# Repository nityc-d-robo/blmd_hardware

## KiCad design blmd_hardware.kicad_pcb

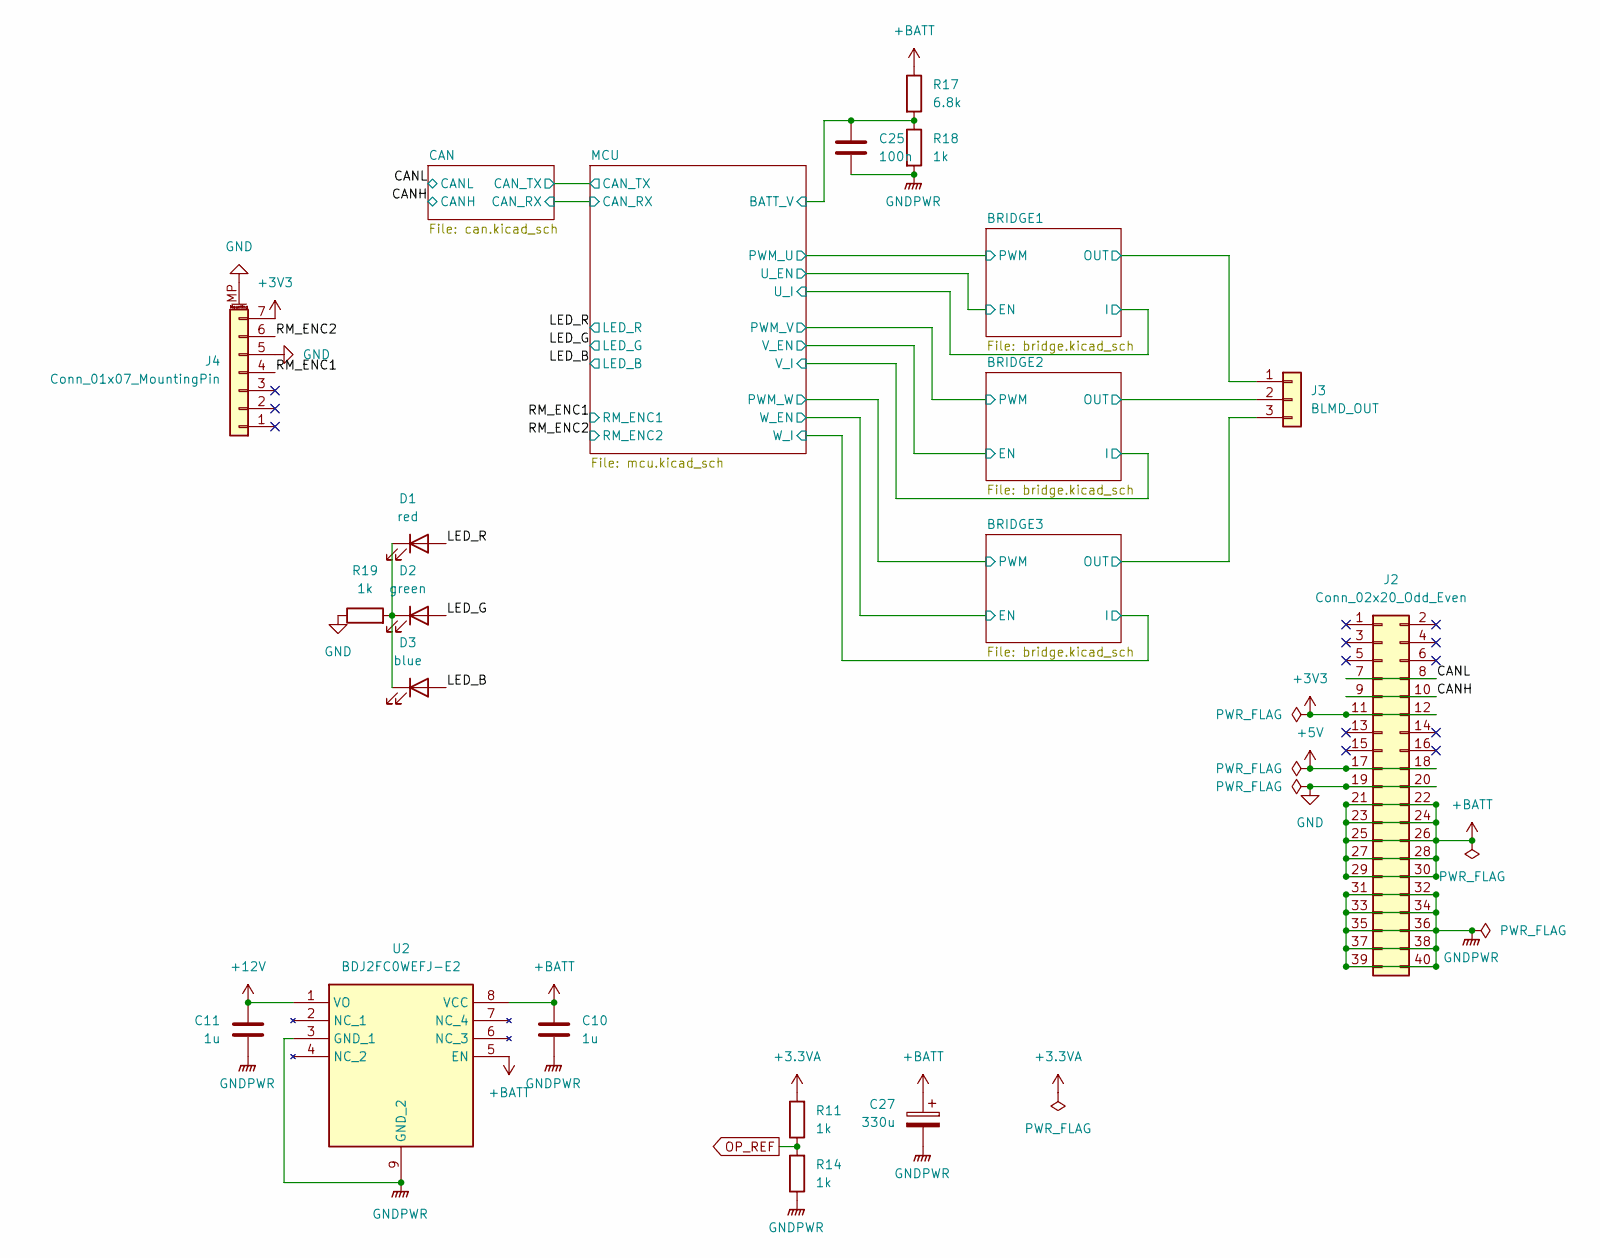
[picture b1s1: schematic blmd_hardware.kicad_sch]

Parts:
C10, C11: 1u; C_0603_1608Metric_Pad1.08x0.95mm_HandSolder
C25: 100n; C_0603_1608Metric_Pad1.08x0.95mm_HandSolder
C27: 330u; CP_Elec_10x12.6
D1: red; LED_0603_1608Metric_Pad1.05x0.95mm_HandSolder
D2: green; LED_0603_1608Metric_Pad1.05x0.95mm_HandSolder
D3: blue; LED_0603_1608Metric_Pad1.05x0.95mm_HandSolder
J2: Conn_02x20_Odd_Even; PinHeader_2x20_P2.54mm_Horizontal
J3: BLMD_OUT; AMASS_MR30PW-FB_1x03_P3.50mm_Horizontal
J4: Conn_01x07_MountingPin; JST_GH_SM07B-GHS-TB_1x07-1MP_P1.25mm_Horizontal
R11, R14, R18, R19: 1k; R_0603_1608Metric_Pad0.98x0.95mm_HandSolder
R17: 6.8k; R_0603_1608Metric_Pad0.98x0.95mm_HandSolder
U2: BDJ2FC0WEFJ-E2; SOIC127P600X100-9N; Manufacturer_Part_Number BDJ2FC0WEFJ-E2

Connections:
+3.3VA: R11.2; also elsewhere on the board
+5V: J2.17, J2.18
+12V: C11.2, U2.1 (VO); also elsewhere on the board
+BATT: C10.2, C27.1, J2.21, J2.22, J2.23, J2.24, J2.25, J2.26, J2.27, J2.28, J2.29, J2.30, R17.1, U2.5 (EN), U2.8 (VCC); also elsewhere on the board
/BRIDGE1/OUT: J3.1; also elsewhere on the board
/BRIDGE2/OUT: J3.2; also elsewhere on the board
/BRIDGE3/OUT: J3.3; also elsewhere on the board
/CANH: J2.9, J2.10; also elsewhere on the board
/CANL: J2.7, J2.8; also elsewhere on the board
/LED_B: D3.2 (A); also elsewhere on the board
/LED_G: D2.2 (A); also elsewhere on the board
/LED_R: D1.2 (A); also elsewhere on the board
/MCU/BATT_V: C25.1, R17.2, R18.1; also elsewhere on the board
/RM_ENC1: J4.4; also elsewhere on the board
/RM_ENC2: J4.6; also elsewhere on the board
GND: J2.19, J2.20, J4.5, J4.MP (MountPin), R19.1; also elsewhere on the board
unnamed: D1.1 (K), D2.1 (K), D3.1 (K), R19.2

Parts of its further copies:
R12: 1k; R_0603_1608Metric_Pad0.98x0.95mm_HandSolder

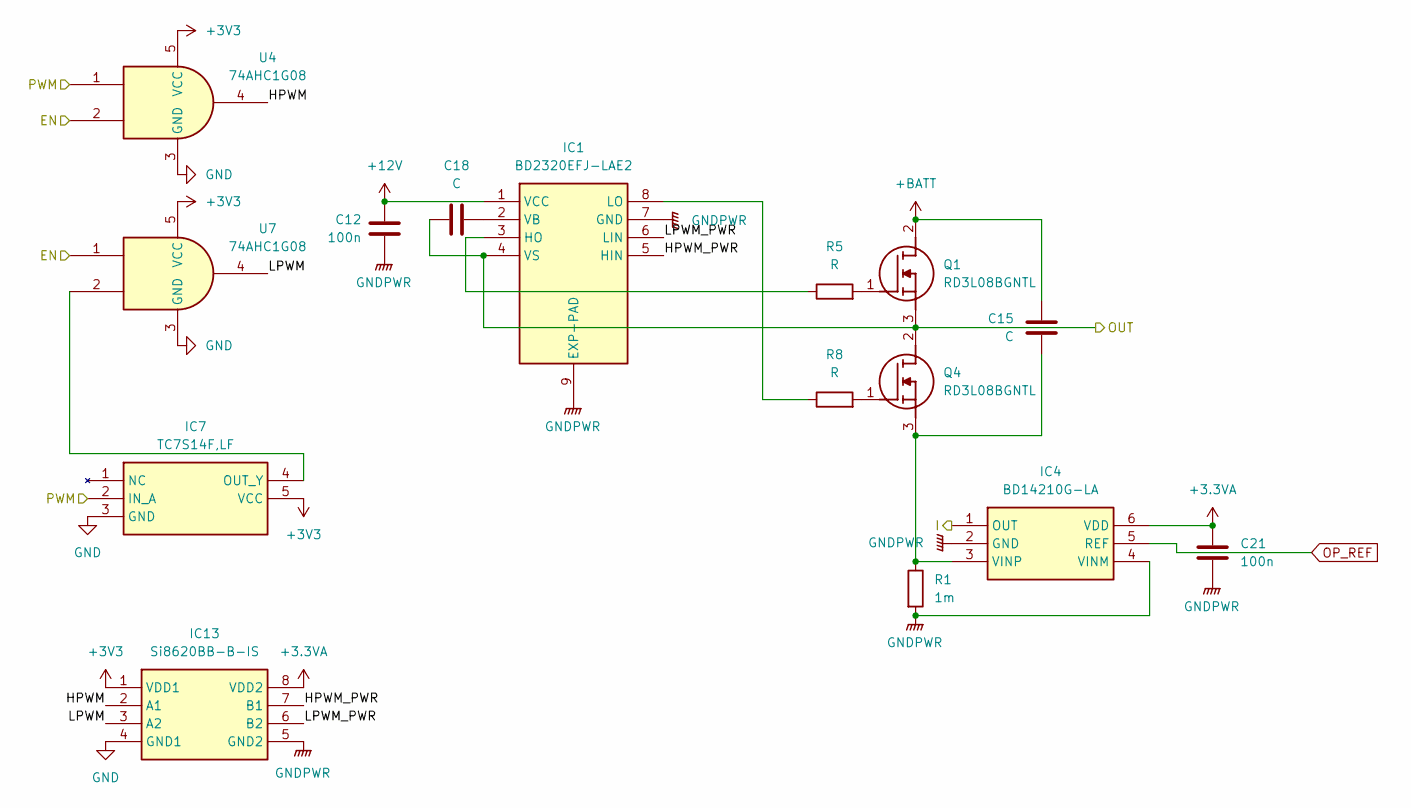
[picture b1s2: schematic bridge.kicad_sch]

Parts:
C12, C21: 100n; C_0603_1608Metric_Pad1.08x0.95mm_HandSolder
C15, C18: C; C_0603_1608Metric_Pad1.08x0.95mm_HandSolder
IC1: BD2320EFJ-LAE2; SOIC127P600X100-9N; Manufacturer_Part_Number BD2320EFJ-LAE2
IC4: BD14210G-LA; SOP95P280X125-6N; Manufacturer_Part_Number BD14210G-LA
IC7: TC7S14F,LF; SOT95P275X140-5N; Manufacturer_Part_Number TC7S14F,LF
IC13: Si8620BB-B-IS; SOIC127P600X175-8N; Manufacturer_Part_Number Si8620BB-B-IS
Q1, Q4: RD3L08BGNTL; RD3P175SNFRATL; Manufacturer_Part_Number RD3L08BGNTL; Mouser Part Number 755-RD3L08BGNTL
R1: 1m; R_0603_1608Metric_Pad0.98x0.95mm_HandSolder
R5, R8: R; R_0603_1608Metric_Pad0.98x0.95mm_HandSolder
U4, U7: 74AHC1G08; SOT95P275X140-5N

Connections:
+3.3VA: C21.1, IC4.6 (VDD), IC13.8 (VDD2); also elsewhere on the board
+12V: C12.2, IC1.1 (VCC); also elsewhere on the board
+BATT: C15.1, Q1.2 (D); also elsewhere on the board
/BRIDGE1/EN: U4.2, U7.1; also elsewhere on the board
/BRIDGE1/HPWM: IC13.2 (A1), U4.4
/BRIDGE1/HPWM_PWR: IC1.5 (HIN), IC13.7 (B1)
/BRIDGE1/I: IC4.1 (OUT); also elsewhere on the board
/BRIDGE1/LPWM: IC13.3 (A2), U7.4
/BRIDGE1/LPWM_PWR: IC1.6 (LIN), IC13.6 (B2)
/BRIDGE1/OUT: C18.1, IC1.4 (VS), Q1.3 (S), Q4.2 (D); also elsewhere on the board
/BRIDGE1/PWM: IC7.2 (IN_A), U4.1; also elsewhere on the board
GND: IC7.3 (GND), IC13.4 (GND1), U4.3 (GND), U7.3 (GND); also elsewhere on the board
unnamed: IC1.3 (HO), R5.1
unnamed: IC1.8 (LO), R8.1
unnamed: C18.2, IC1.2 (VB)
unnamed: C15.2, IC4.3 (VINP), Q4.3 (S), R1.1
unnamed: IC7.4 (OUT_Y), U7.2
unnamed: Q1.1 (G), R5.2
unnamed: Q4.1 (G), R8.2

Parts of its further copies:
C13, C14, C22, C23: 100n; C_0603_1608Metric_Pad1.08x0.95mm_HandSolder
C16, C17, C19, C20: C; C_0603_1608Metric_Pad1.08x0.95mm_HandSolder
IC2, IC3: BD2320EFJ-LAE2; SOIC127P600X100-9N; Manufacturer_Part_Number BD2320EFJ-LAE2
IC5, IC6: BD14210G-LA; SOP95P280X125-6N; Manufacturer_Part_Number BD14210G-LA
IC8, IC9: TC7S14F,LF; SOT95P275X140-5N; Manufacturer_Part_Number TC7S14F,LF
IC14, IC15: Si8620BB-B-IS; SOIC127P600X175-8N; Manufacturer_Part_Number Si8620BB-B-IS
Q2, Q3, Q5, Q6: RD3L08BGNTL; RD3P175SNFRATL; Manufacturer_Part_Number RD3L08BGNTL; Mouser Part Number 755-RD3L08BGNTL
R2, R3: 1m; R_0603_1608Metric_Pad0.98x0.95mm_HandSolder
R6, R7, R9, R10: R; R_0603_1608Metric_Pad0.98x0.95mm_HandSolder
U5, U6, U8, U9: 74AHC1G08; SOT95P275X140-5N

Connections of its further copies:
+3.3VA: C22.1, C23.1, IC5.6 (VDD), IC6.6 (VDD), IC14.8 (VDD2), IC15.8 (VDD2); also elsewhere on the board
+12V: C13.2, C14.2, IC2.1 (VCC), IC3.1 (VCC); also elsewhere on the board
+BATT: C16.1, C17.1, Q2.2 (D), Q3.2 (D); also elsewhere on the board
/BRIDGE2/EN: U5.2, U8.1; also elsewhere on the board
/BRIDGE2/HPWM: IC14.2 (A1), U5.4
/BRIDGE2/HPWM_PWR: IC2.5 (HIN), IC14.7 (B1)
/BRIDGE2/I: IC5.1 (OUT); also elsewhere on the board
/BRIDGE2/LPWM: IC14.3 (A2), U8.4
/BRIDGE2/LPWM_PWR: IC2.6 (LIN), IC14.6 (B2)
/BRIDGE2/OUT: C19.1, IC2.4 (VS), Q2.3 (S), Q5.2 (D); also elsewhere on the board
/BRIDGE2/PWM: IC8.2 (IN_A), U5.1; also elsewhere on the board
/BRIDGE3/EN: U6.2, U9.1; also elsewhere on the board
/BRIDGE3/HPWM: IC15.2 (A1), U6.4
/BRIDGE3/HPWM_PWR: IC3.5 (HIN), IC15.7 (B1)
/BRIDGE3/I: IC6.1 (OUT); also elsewhere on the board
/BRIDGE3/LPWM: IC15.3 (A2), U9.4
/BRIDGE3/LPWM_PWR: IC3.6 (LIN), IC15.6 (B2)
/BRIDGE3/OUT: C20.1, IC3.4 (VS), Q3.3 (S), Q6.2 (D); also elsewhere on the board
/BRIDGE3/PWM: IC9.2 (IN_A), U6.1; also elsewhere on the board
GND: IC8.3 (GND), IC9.3 (GND), IC14.4 (GND1), IC15.4 (GND1), U5.3 (GND), U6.3 (GND), U8.3 (GND), U9.3 (GND); also elsewhere on the board
unnamed: IC2.3 (HO), R6.1
unnamed: IC2.8 (LO), R9.1
unnamed: C19.2, IC2.2 (VB)
unnamed: IC3.3 (HO), R7.1
unnamed: IC3.8 (LO), R10.1
unnamed: C20.2, IC3.2 (VB)
unnamed: C16.2, IC5.3 (VINP), Q5.3 (S), R2.1
unnamed: C17.2, IC6.3 (VINP), Q6.3 (S), R3.1
unnamed: IC8.4 (OUT_Y), U8.2
unnamed: IC9.4 (OUT_Y), U9.2
unnamed: Q2.1 (G), R6.2
unnamed: Q3.1 (G), R7.2
unnamed: Q5.1 (G), R9.2
unnamed: Q6.1 (G), R10.2

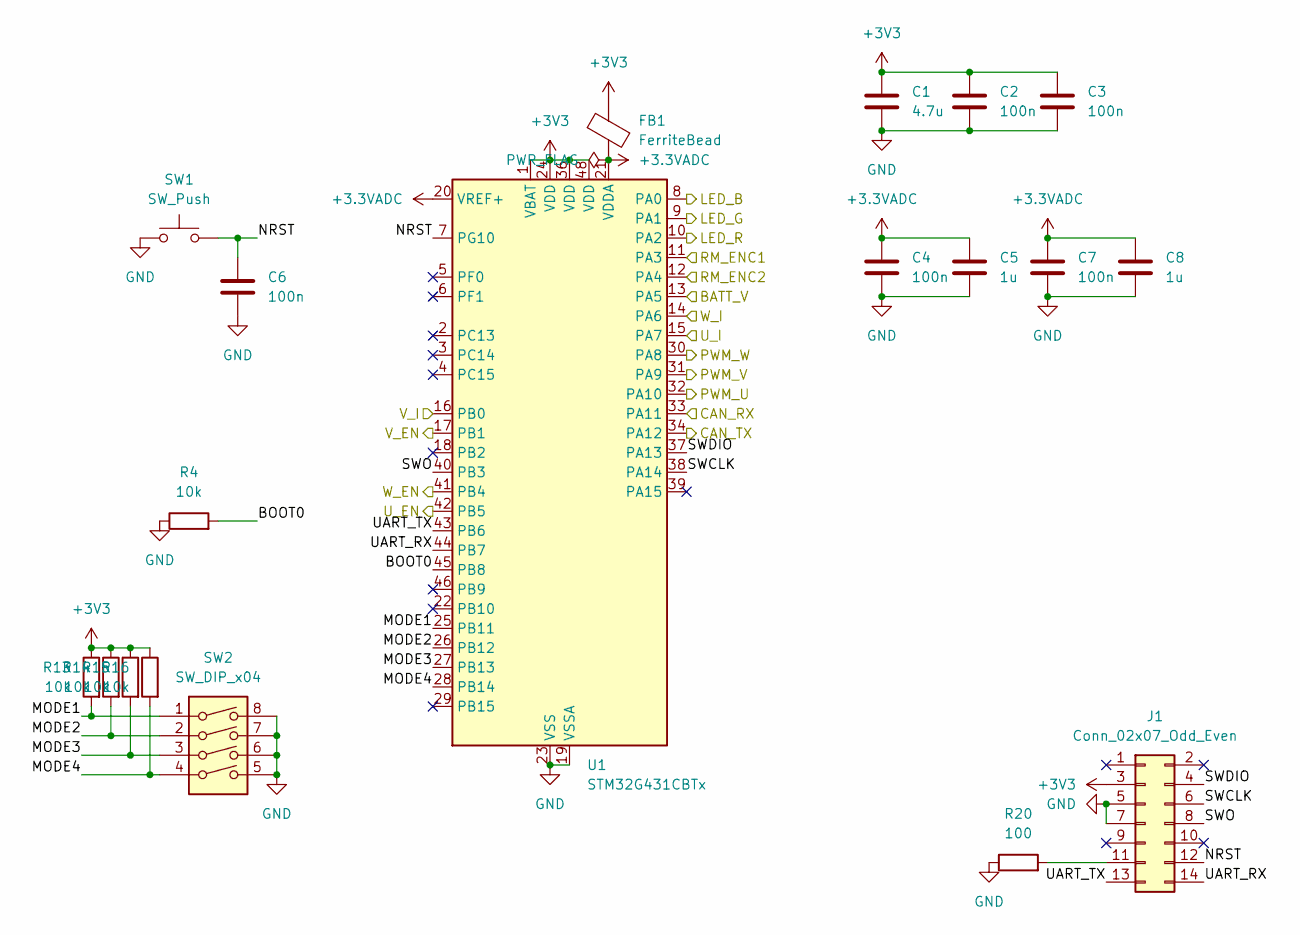
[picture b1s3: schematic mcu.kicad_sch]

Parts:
C1: 4.7u; C_0603_1608Metric_Pad1.08x0.95mm_HandSolder
C2, C3, C4, C6, C7: 100n; C_0603_1608Metric_Pad1.08x0.95mm_HandSolder
C5, C8: 1u; C_0603_1608Metric_Pad1.08x0.95mm_HandSolder
FB1: FerriteBead; C_0603_1608Metric_Pad1.08x0.95mm_HandSolder
J1: Conn_02x07_Odd_Even; PinHeader_2x07_P1.27mm_Vertical
R4, R13, R14, R15, R16: 10k; R_0603_1608Metric_Pad0.98x0.95mm_HandSolder
R20: 100; R_0603_1608Metric_Pad0.98x0.95mm_HandSolder
SW1: SW_Push; TVAF06-A020B-R
SW2: SW_DIP_x04; SW_DIP_SPSTx04_Slide_Copal_CHS-04B_W7.62mm_P1.27mm
U1: STM32G431CBTx; LQFP-48_7x7mm_P0.5mm

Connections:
+3.3VADC: C4.1, C5.1, C7.1, C8.1, FB1.2, U1.20 (VREF+), U1.21 (VDDA)
/BRIDGE1/EN: U1.42 (PB5); also elsewhere on the board
/BRIDGE1/I: U1.15 (PA7); also elsewhere on the board
/BRIDGE1/PWM: U1.32 (PA10); also elsewhere on the board
/BRIDGE2/EN: U1.17 (PB1); also elsewhere on the board
/BRIDGE2/I: U1.16 (PB0); also elsewhere on the board
/BRIDGE2/PWM: U1.31 (PA9); also elsewhere on the board
/BRIDGE3/EN: U1.41 (PB4); also elsewhere on the board
/BRIDGE3/I: U1.14 (PA6); also elsewhere on the board
/BRIDGE3/PWM: U1.30 (PA8); also elsewhere on the board
/CAN/CAN_RX: U1.33 (PA11); also elsewhere on the board
/CAN/CAN_TX: U1.34 (PA12); also elsewhere on the board
/LED_B: U1.8 (PA0); also elsewhere on the board
/LED_G: U1.9 (PA1); also elsewhere on the board
/LED_R: U1.10 (PA2); also elsewhere on the board
/MCU/BATT_V: U1.13 (PA5); also elsewhere on the board
/MCU/BOOT0: R4.2, U1.45 (PB8)
/MCU/MODE1: R13.2, SW2.1, U1.25 (PB11)
/MCU/MODE3: R15.2, SW2.3, U1.27 (PB13)
/MCU/MODE4: R16.2, SW2.4, U1.28 (PB14)
/MCU/NRST: C6.1, J1.12, SW1.2, U1.7 (PG10)
/MCU/SWCLK: J1.6, U1.38 (PA14)
/MCU/SWDIO: J1.4, U1.37 (PA13)
/MCU/SWO: J1.8, U1.40 (PB3)
/MCU/UART_RX: J1.14, U1.44 (PB7)
/MCU/UART_TX: J1.13, U1.43 (PB6)
/RM_ENC1: U1.11 (PA3); also elsewhere on the board
/RM_ENC2: U1.12 (PA4); also elsewhere on the board
GND: C1.2, C2.2, C3.2, C4.2, C5.2, C6.2, C7.2, C8.2, J1.5, J1.7, R4.1, R20.1, SW1.1, SW2.5, SW2.6, SW2.7, SW2.8, U1.19 (VSSA), U1.23 (VSS), U1.35 (VSS), U1.47 (VSS); also elsewhere on the board
unnamed: J1.11, R20.2

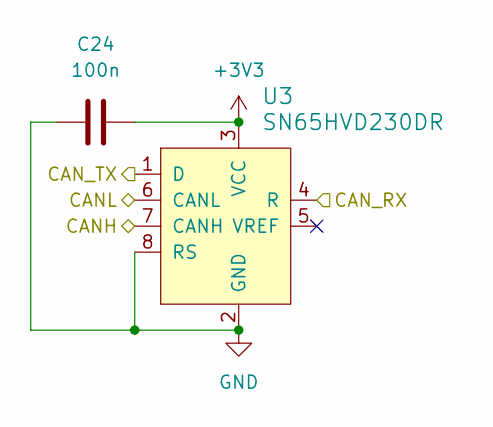
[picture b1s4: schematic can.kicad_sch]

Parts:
C24: 100n; C_0603_1608Metric_Pad1.08x0.95mm_HandSolder
U3: SN65HVD230DR; SOIC-8_3.9x4.9mm_P1.27mm; MPN SN65HVD230DR; Digi-Key_PN 296-11654-1-ND

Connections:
/CAN/CAN_RX: U3.4 (R); also elsewhere on the board
/CAN/CAN_TX: U3.1 (D); also elsewhere on the board
/CANH: U3.7 (CANH); also elsewhere on the board
/CANL: U3.6 (CANL); also elsewhere on the board
GND: C24.1, U3.2 (GND), U3.8 (RS); also elsewhere on the board

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
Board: 2 copper layers, 82 parts (45 on the bottom side), 77 nets, no tracks yet.

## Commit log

2024-01-13 first commit.
2024-01-14 回路図ほぼ完成 MOSFETのゲート抵抗の決め方よくわかんないです助けて
2024-01-15 部品配置完了(暫定)
